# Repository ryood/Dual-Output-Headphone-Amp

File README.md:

Dual-Output-Headphone-Amp
=========================

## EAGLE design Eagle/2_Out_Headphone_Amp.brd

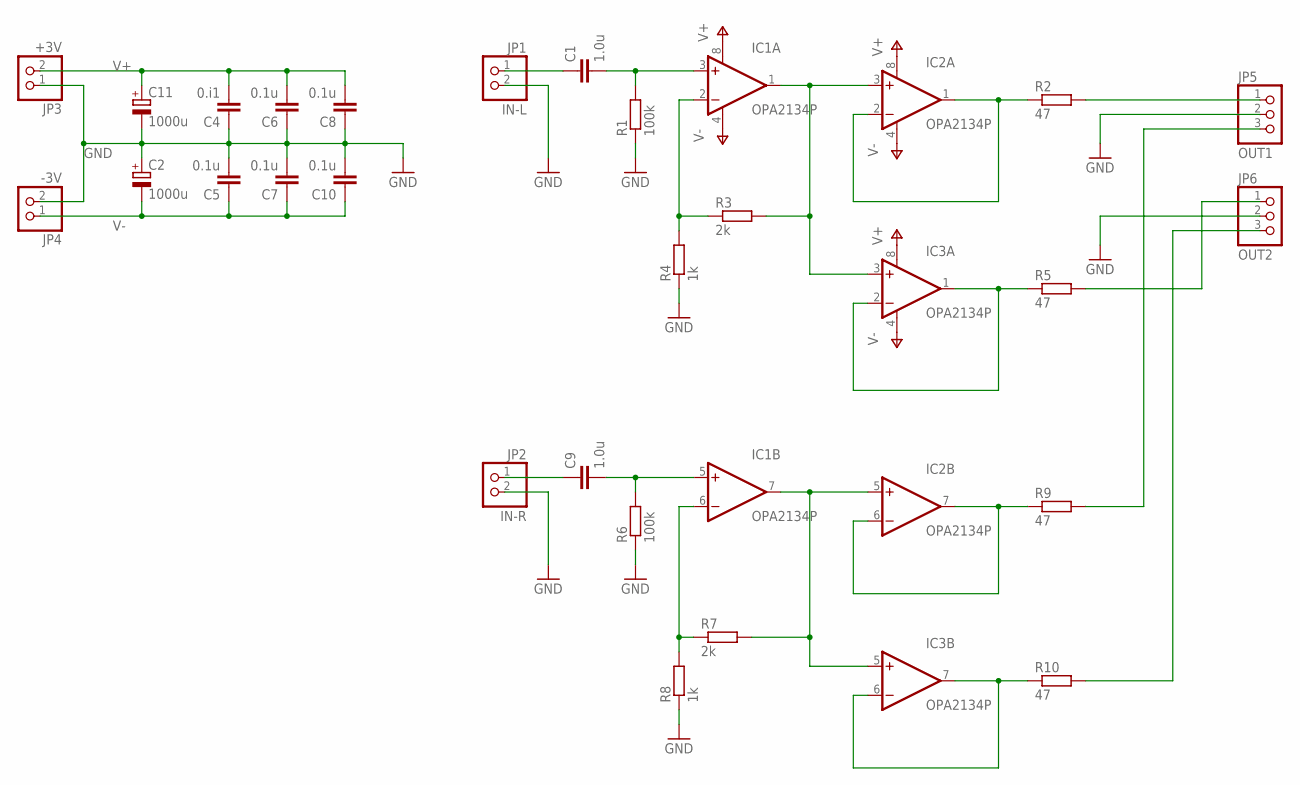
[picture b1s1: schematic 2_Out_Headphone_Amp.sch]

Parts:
C1, C9: 1.0u; C050-045X075
C2, C11: 1000u; TT5D11L
C4: 0.i1; C050-024X044
C5, C6, C7, C8, C10: 0.1u; C050-024X044
IC1, IC2, IC3: OPA2134P; DIL08
JP1: IN-L; 1X02
JP2: IN-R; 1X02
JP3: +3V; 1X02
JP4: -3V; 1X02
JP5: OUT1; 1X03
JP6: OUT2; 1X03
R1, R6: 100k; 0207/2V
R2, R5, R9, R10: 47; 0207/7
R3: 2k; 0207/7
R4, R8: 1k; 0207/2V
R7: 2k; 0207/2V

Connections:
GND: C2.+, C4.1, C5.2, C6.1, C7.2, C8.1, C10.2, C11.-, JP1.2, JP2.2, JP3.1, JP4.2, JP5.2, JP6.2, R1.1, R4.1, R6.1, R8.1
unnamed: C1.1, JP1.1
unnamed: C1.2, IC1.3 (+IN), R1.2
unnamed: IC1.2 (-IN), R3.1, R4.2
unnamed: IC1.1 (OUT), IC2.3 (+IN), IC3.3 (+IN), R3.2
unnamed: IC2.1 (OUT), IC2.2 (-IN), R2.1
unnamed: JP5.1, R2.2
unnamed: IC3.1 (OUT), IC3.2 (-IN), R5.1
unnamed: JP6.1, R5.2
unnamed: C9.1, JP2.1
unnamed: C9.2, IC1.5 (+IN), R6.2
unnamed: IC1.6 (-IN), R7.1, R8.2
unnamed: IC1.7 (OUT), IC2.5 (+IN), IC3.5 (+IN), R7.2
unnamed: IC2.6 (-IN), IC2.7 (OUT), R9.1
unnamed: IC3.6 (-IN), IC3.7 (OUT), R10.1
unnamed: JP5.3, R9.2
unnamed: JP6.3, R10.2
V+: C4.2, C6.2, C8.2, C11.+, IC1.8 (V+), IC2.8 (V+), IC3.8 (V+), JP3.2
V-: C2.-, C5.1, C7.1, C10.1, IC1.4 (V-), IC2.4 (V-), IC3.4 (V-), JP4.1

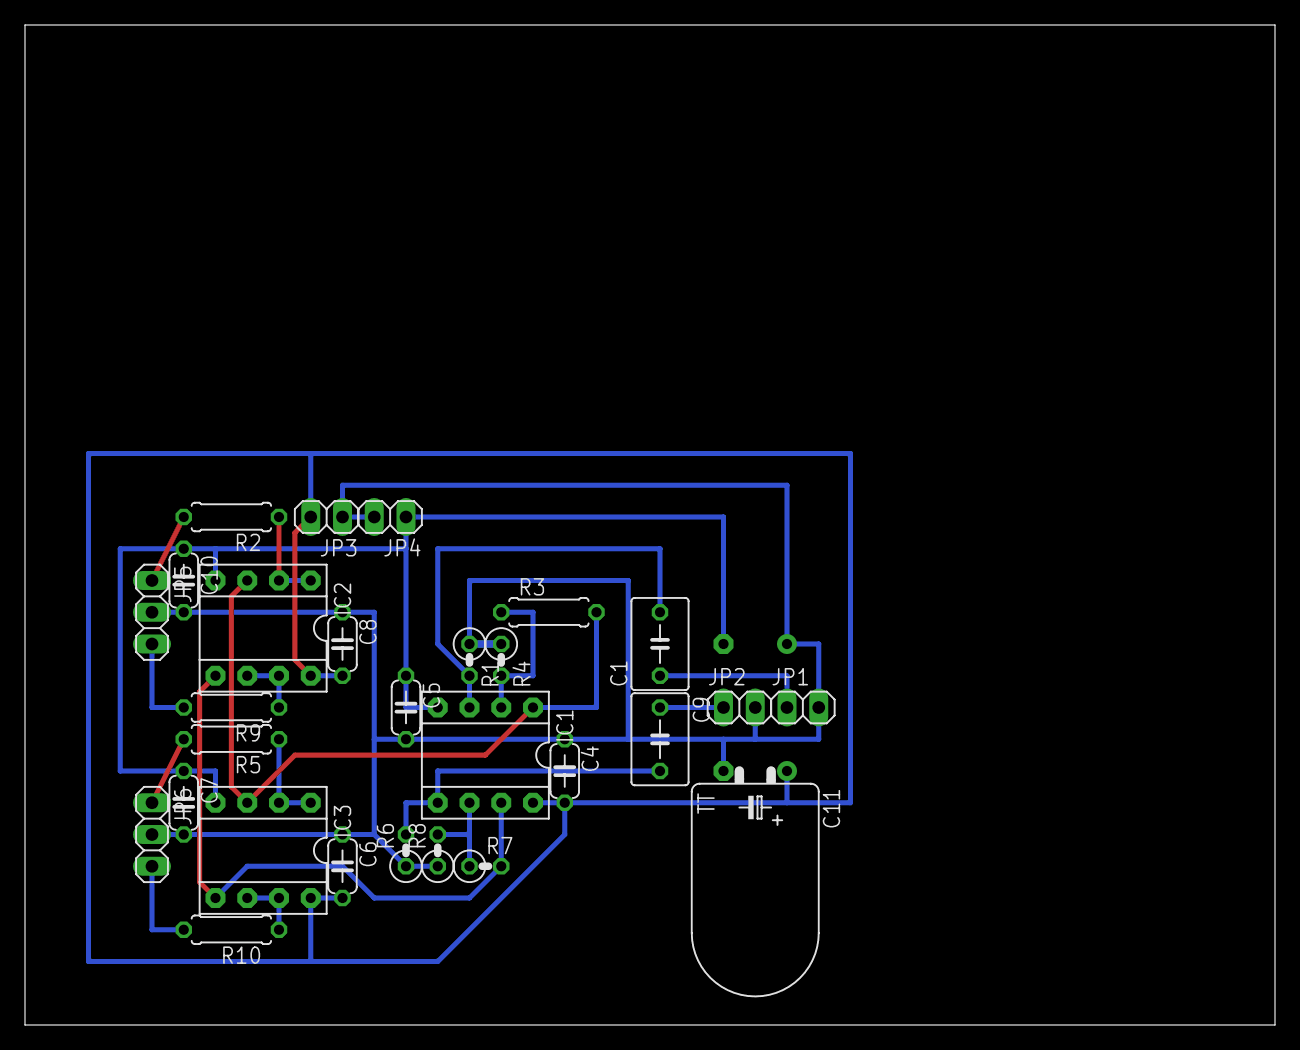
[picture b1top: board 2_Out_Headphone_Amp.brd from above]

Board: 2 copper layers, 100.0 x 80.0 mm, 29 parts (1 on the bottom side), 19 nets.

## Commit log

2014-10-19 ヘッドホンアンプの修正
2014-10-24 回路図修正
2014-10-26 基板設計図追加
2014-10-26 基板設計図修正
2014-10-27 基板配線図修正 Cサイズフルに
2014-10-27 基板設計図微調整前
2014-10-27 基板設計図 抵抗を立てる前
2014-10-29 基板設計図の変更
